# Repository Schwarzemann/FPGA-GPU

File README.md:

# FPGA-GPU
An FPGA GPU designed in KiCAD

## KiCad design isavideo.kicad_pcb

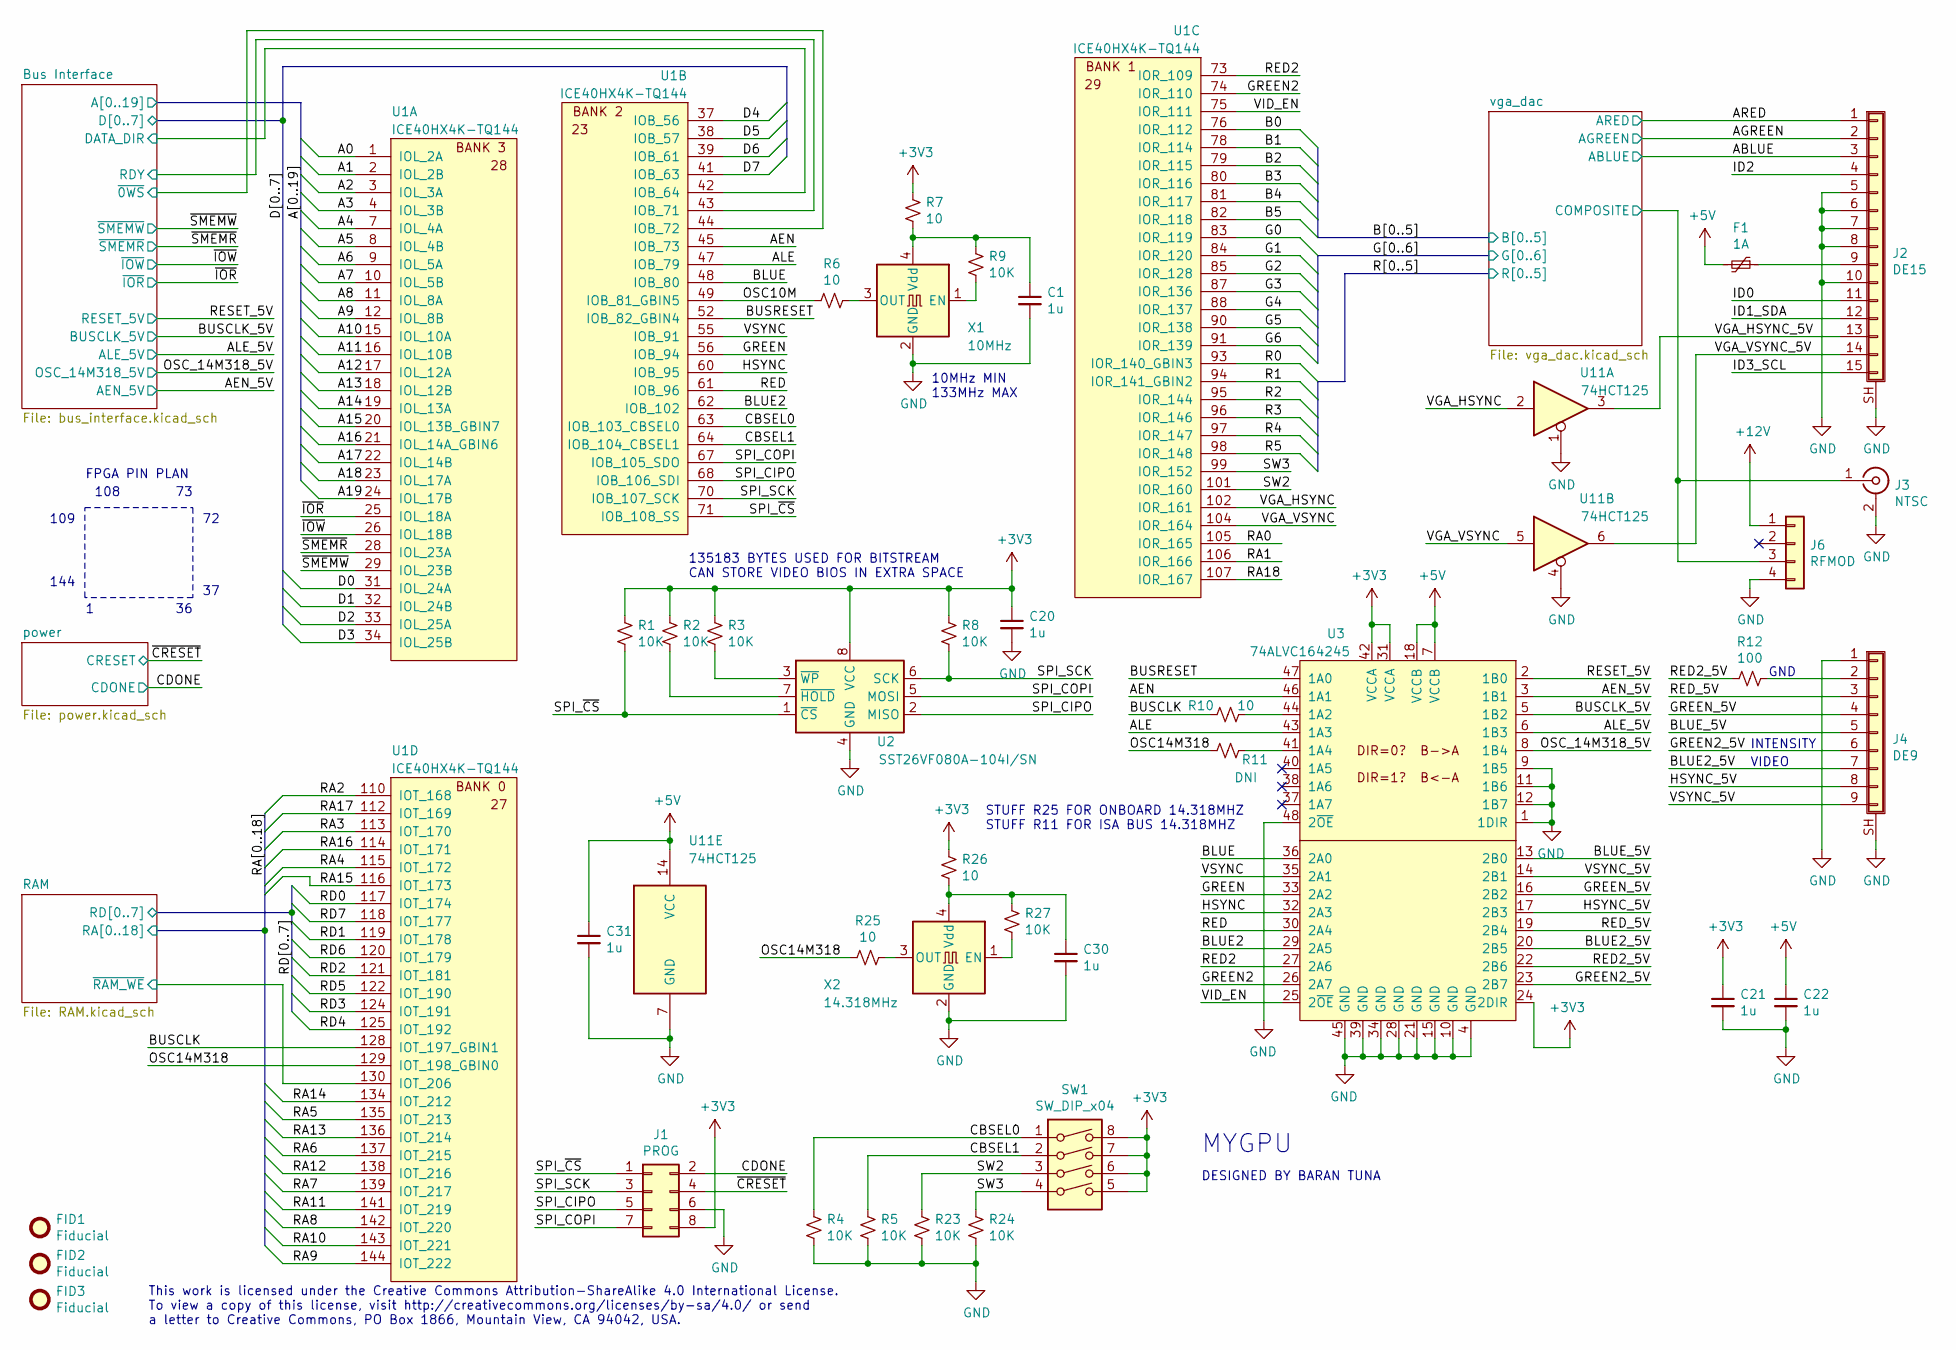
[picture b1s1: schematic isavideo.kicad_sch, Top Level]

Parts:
C1, C20, C21, C22, C30, C31: 1u; CAPC1608X100; Mouser 810-CGA3E1X7R1C105AC
F1: 1A; RESC3216X70; Mouser 530-0ZCJ0050FF2G
FID1, FID2, FID3: Fiducial; Fiducial_1mm_Dia_2mm_Outer
J1: PROG; Pin_Header_Straight_2x04_Pitch2.54mm
J2: DE15; DB15HDFC; Mouser 156-3315-E
J3: NTSC; KOBICONN_161-03X0-E; Mouser 161-0360-E
J4: DE9; DB9FC2; Mouser 152-3409
J6: RFMOD; Pin_Header_Straight_1x04_Pitch2.54mm
R1, R2, R3, R4, R5, R8, R9, R23, R24, R27: 10K; RESC1608X55; Mouser 603-RC0603FR-0710KL
R6, R7, R10, R25, R26: 10; RESC1608X55; Mouser 603-RC0603FR-0710RL
R11: DNI; RESC1608X55; Mouser DNI
R12: 100; RESC1608X55; Mouser 603-RC0603FR-07100RL
SW1: SW_DIP_x04; SW_DIP254P762X635-8; Mouser 706-76PSB04ST
U1: ICE40HX4K-TQ144; TSQFP50P2200X2200X160-144; Mouser 842-ICE40HX4K-TQ144
U2: SST26VF080A-104I/SN; SOP127P620X175-8; Mouser 579-26VF080A-104I/SN
U3: 74ALVC164245; TSSOP50P810X120-48; Mouser 771-74ALVC164245
U11: 74HCT125; TSOP65P640X110-14; Mouser 771-74HCT125PW-T
X1: 10MHz; XTAL320X250X120-4; Mouser 520-ECS-2333-100-BNT
X2: 14.318MHz; XTAL320X250X120-4; Mouser 815-ASE-14.318MLCT

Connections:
+3V3: C20.1, C21.1, J1.8, R1.1, R2.1, R3.1, R7.1, R8.1, R26.1, SW1.5, SW1.6, SW1.7, SW1.8, U2.8 (VCC), U3.24 (2DIR), U3.31 (VCCA), U3.42 (VCCA); also elsewhere on the board
+5V: C22.1, C31.1, F1.2, U3.7 (VCCB), U3.18 (VCCB), U11.14 (VCC); also elsewhere on the board
+12V: J6.1; also elsewhere on the board
/A0: U1.1 (IOL_2A); also elsewhere on the board
/A1: U1.2 (IOL_2B); also elsewhere on the board
/A2: U1.3 (IOL_3A); also elsewhere on the board
/A3: U1.4 (IOL_3B); also elsewhere on the board
/A4: U1.7 (IOL_4A); also elsewhere on the board
/A5: U1.8 (IOL_4B); also elsewhere on the board
/A6: U1.9 (IOL_5A); also elsewhere on the board
/A7: U1.10 (IOL_5B); also elsewhere on the board
/A8: U1.11 (IOL_8A); also elsewhere on the board
/A9: U1.12 (IOL_8B); also elsewhere on the board
/A10: U1.15 (IOL_10A); also elsewhere on the board
/A11: U1.16 (IOL_10B); also elsewhere on the board
/A12: U1.17 (IOL_12A); also elsewhere on the board
/A13: U1.18 (IOL_12B); also elsewhere on the board
/A14: U1.19 (IOL_13A); also elsewhere on the board
/A15: U1.20 (IOL_13B_GBIN7); also elsewhere on the board
/A16: U1.21 (IOL_14A_GBIN6); also elsewhere on the board
/A17: U1.22 (IOL_14B); also elsewhere on the board
/A18: U1.23 (IOL_17A); also elsewhere on the board
/A19: U1.24 (IOL_17B); also elsewhere on the board
/ABLUE: J2.3; also elsewhere on the board
/AEN: U1.45 (IOB_73), U3.46 (1A1)
/AEN_5V: U3.3 (1B1); also elsewhere on the board
/AGREEN: J2.2; also elsewhere on the board
/ALE: U1.47 (IOB_79), U3.43 (1A3)
/ALE_5V: U3.6 (1B3); also elsewhere on the board
/ARED: J2.1; also elsewhere on the board
/B0: U1.76 (IOR_112); also elsewhere on the board
/B1: U1.78 (IOR_114); also elsewhere on the board
/B2: U1.79 (IOR_115); also elsewhere on the board
/B3: U1.80 (IOR_116); also elsewhere on the board
/B4: U1.81 (IOR_117); also elsewhere on the board
/B5: U1.82 (IOR_118); also elsewhere on the board
/BLUE: U1.48 (IOB_80), U3.36 (2A0)
/BLUE2: U1.62 (IOB_102), U3.29 (2A5)
/BLUE2_5V: J4.7, U3.20 (2B5)
/BLUE_5V: J4.5, U3.13 (2B0)
/BUSCLK: R10.2, U1.128 (IOT_197_GBIN1)
/BUSCLK_5V: U3.5 (1B2); also elsewhere on the board
/BUSRESET: U1.52 (IOB_82_GBIN4), U3.47 (1A0)
/Bus Interface/DATA_DIR: U1.42 (IOB_64); also elsewhere on the board
/Bus Interface/RDY: U1.43 (IOB_71); also elsewhere on the board
/Bus Interface/~0WS: U1.44 (IOB_72); also elsewhere on the board
/CBSEL0: R4.1, SW1.1, U1.63 (IOB_103_CBSEL0)
/CBSEL1: R5.1, SW1.2, U1.64 (IOB_104_CBSEL1)
/CDONE: J1.2; also elsewhere on the board
/D0: U1.31 (IOL_24A); also elsewhere on the board
/D1: U1.32 (IOL_24B); also elsewhere on the board
/D2: U1.33 (IOL_25A); also elsewhere on the board
/D3: U1.34 (IOL_25B); also elsewhere on the board
/D4: U1.37 (IOB_56); also elsewhere on the board
/D5: U1.38 (IOB_57); also elsewhere on the board
/D6: U1.39 (IOB_61); also elsewhere on the board
/D7: U1.41 (IOB_63); also elsewhere on the board
/G0: U1.83 (IOR_119); also elsewhere on the board
/G1: U1.84 (IOR_120); also elsewhere on the board
/G2: U1.85 (IOR_128); also elsewhere on the board
/G3: U1.87 (IOR_136); also elsewhere on the board
/G4: U1.88 (IOR_137); also elsewhere on the board
/G5: U1.90 (IOR_138); also elsewhere on the board
/G6: U1.91 (IOR_139); also elsewhere on the board
/GREEN: U1.56 (IOB_94), U3.33 (2A2)
/GREEN2: U1.74 (IOR_110), U3.26 (2A7)
/GREEN2_5V: J4.6, U3.23 (2B7)
/GREEN_5V: J4.4, U3.16 (2B2)
/HSYNC: U1.60 (IOB_95), U3.32 (2A3)
/HSYNC_5V: J4.8, U3.17 (2B3)
/OSC10M: R6.2, U1.49 (IOB_81_GBIN5)
/OSC14M318: R11.2, R25.2, U1.129 (IOT_198_GBIN0)
/OSC_14M318_5V: U3.8 (1B4); also elsewhere on the board
/R0: U1.93 (IOR_140_GBIN3); also elsewhere on the board
/R1: U1.94 (IOR_141_GBIN2); also elsewhere on the board
/R2: U1.95 (IOR_144); also elsewhere on the board
/R3: U1.96 (IOR_146); also elsewhere on the board
/R4: U1.97 (IOR_147); also elsewhere on the board
/R5: U1.98 (IOR_148); also elsewhere on the board
/RA0: U1.105 (IOR_165); also elsewhere on the board
/RA1: U1.106 (IOR_166); also elsewhere on the board
/RA2: U1.110 (IOT_168); also elsewhere on the board
/RA3: U1.113 (IOT_170); also elsewhere on the board
/RA4: U1.115 (IOT_172); also elsewhere on the board
/RA5: U1.135 (IOT_213); also elsewhere on the board
/RA6: U1.137 (IOT_215); also elsewhere on the board
/RA7: U1.139 (IOT_217); also elsewhere on the board
/RA8: U1.142 (IOT_220); also elsewhere on the board
/RA9: U1.144 (IOT_222); also elsewhere on the board
/RA10: U1.143 (IOT_221); also elsewhere on the board
/RA11: U1.141 (IOT_219); also elsewhere on the board
/RA12: U1.138 (IOT_216); also elsewhere on the board
/RA13: U1.136 (IOT_214); also elsewhere on the board
/RA14: U1.134 (IOT_212); also elsewhere on the board
/RA15: U1.116 (IOT_173); also elsewhere on the board
/RA16: U1.114 (IOT_171); also elsewhere on the board
/RA17: U1.112 (IOT_169); also elsewhere on the board
/RA18: U1.107 (IOR_167); also elsewhere on the board
/RAM/~RAM_WE: U1.130 (IOT_206); also elsewhere on the board
/RD0: U1.117 (IOT_174); also elsewhere on the board
/RD1: U1.119 (IOT_178); also elsewhere on the board
/RD2: U1.121 (IOT_181); also elsewhere on the board
/RD3: U1.124 (IOT_191); also elsewhere on the board
/RD4: U1.125 (IOT_192); also elsewhere on the board
/RD5: U1.122 (IOT_190); also elsewhere on the board
/RD6: U1.120 (IOT_179); also elsewhere on the board
/RD7: U1.118 (IOT_177); also elsewhere on the board
/RED: U1.61 (IOB_96), U3.30 (2A4)
/RED2: U1.73 (IOR_109), U3.27 (2A6)
/RED2_5V: R12.2, U3.22 (2B6)
/RED_5V: J4.3, U3.19 (2B4)
/RESET_5V: U3.2 (1B0); also elsewhere on the board
/SPI_CIPO: J1.5, U1.68 (IOB_106_SDI), U2.2 (MISO)
/SPI_COPI: J1.7, U1.67 (IOB_105_SDO), U2.5 (MOSI)
/SPI_SCK: J1.3, R8.2, U1.70 (IOB_107_SCK), U2.6 (SCK)
/SPI_~CS: J1.1, R1.2, U1.71 (IOB_108_SS), U2.1 (~CS)
/SW2: R23.1, SW1.3, U1.101 (IOR_160)
/SW3: R24.1, SW1.4, U1.99 (IOR_152)
/VGA_HSYNC: U1.102 (IOR_161), U11.2
/VGA_HSYNC_5V: J2.13, U11.3
/VGA_VSYNC: U1.104 (IOR_164), U11.5
/VGA_VSYNC_5V: J2.14, U11.6
/VID_EN: U1.75 (IOR_111), U3.25 (2~OE)
/VSYNC: U1.55 (IOB_91), U3.35 (2A1)
/VSYNC_5V: J4.9, U3.14 (2B1)
/vga_dac/COMPOSITE: J3.1 (In), J6.3; also elsewhere on the board
/~CRESET: J1.4; also elsewhere on the board
/~IOR: U1.25 (IOL_18A); also elsewhere on the board
/~IOW: U1.26 (IOL_18B); also elsewhere on the board
/~SMEMR: U1.28 (IOL_23A); also elsewhere on the board
/~SMEMW: U1.29 (IOL_23B); also elsewhere on the board
GND: C1.2, C20.2, C21.2, C22.2, C30.2, C31.2, J1.6, J2.5, J2.6, J2.7, J2.8, J2.10, J2.SH (Shield), J3.2 (Ext), J4.1, J4.SH (Shield), J6.4, R4.2, R5.2, R23.2, R24.2, U2.4 (GND), U3.1 (1DIR), U3.4 (GND), U3.9 (1B5), U3.10 (GND), U3.11 (1B6), U3.12 (1B7), U3.15 (GND), U3.21 (GND), U3.28 (GND), U3.34 (GND), U3.39 (GND), U3.45 (GND), U3.48 (2~OE), U11.1, U11.4, U11.7 (GND), X1.2 (GND), X2.2 (GND); also elsewhere on the board
unnamed: C1.1, R7.2, R9.1, X1.4 (Vdd)
unnamed: C30.1, R26.2, R27.1, X2.4 (Vdd)
unnamed: F1.1, J2.9
unnamed: J4.2, R12.1
unnamed: R2.2, U2.7 (~HOLD)
unnamed: R3.2, U2.3 (~WP)
unnamed: R6.1, X1.3 (OUT)
unnamed: R9.2, X1.1 (EN)
unnamed: R10.1, U3.44 (1A2)
unnamed: R11.1, U3.41 (1A4)
unnamed: R25.1, X2.3 (OUT)
unnamed: R27.2, X2.1 (EN)

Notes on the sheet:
STUFF R25 FOR ONBOARD 14.318MHZ STUFF R11 FOR ISA BUS 14.318MHZ
FPGA PIN PLAN
DESIGNED BY BARAN TUNA
108
VIDEO
GND
144
135183 BYTES USED FOR BITSTREAM CAN STORE VIDEO BIOS IN EXTRA SPACE
109
INTENSITY
MYGPU
This work is licensed under the Creative Commons Attribution-ShareAlike 4.0 International License. To view a copy of this license, visit http://creativecommons.org/licenses/by-sa/4.0/ or send a letter to Creative Commons, PO Box 1866, Mountain View, CA 94042, USA.
10MHz MIN 133MHz MAX

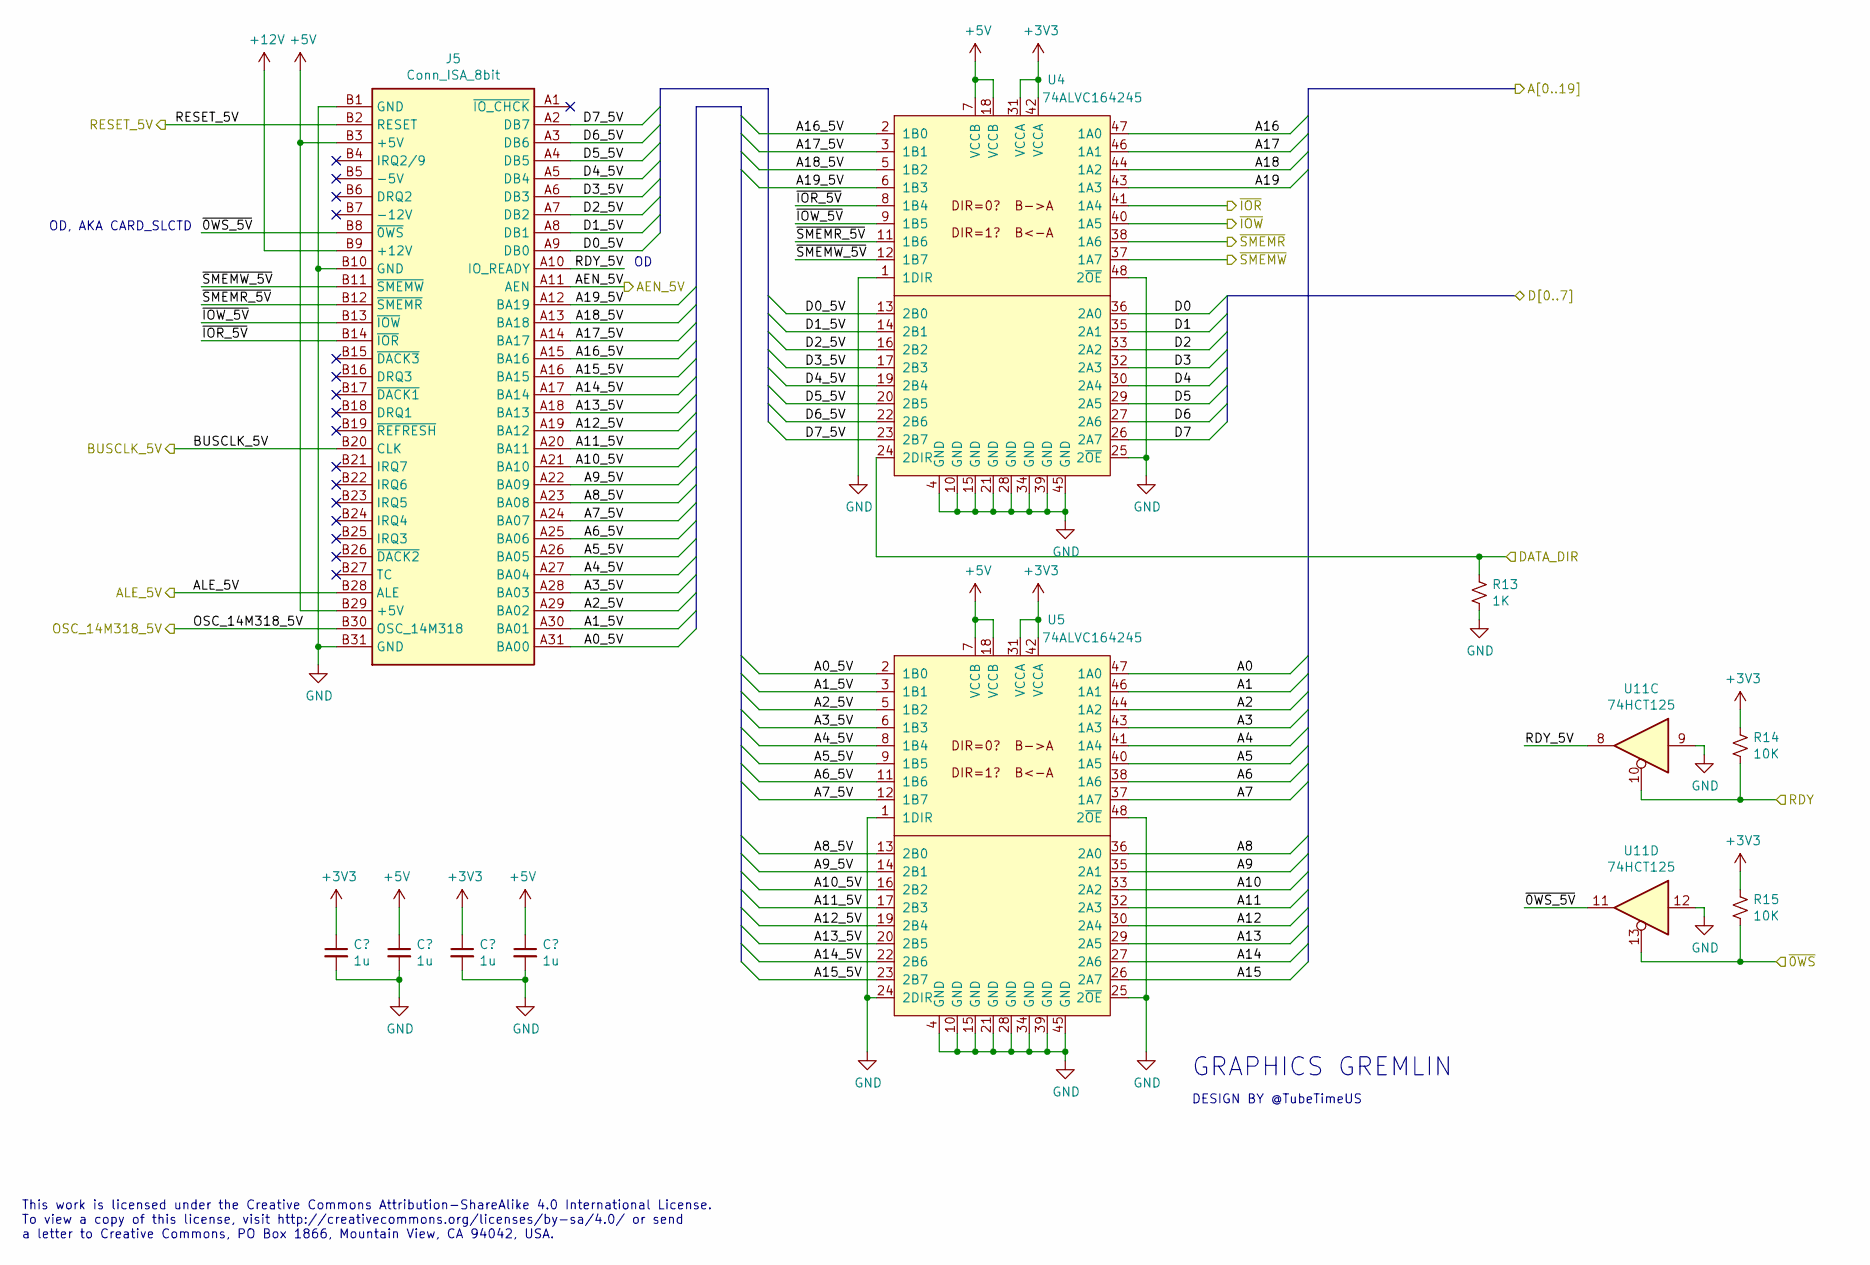
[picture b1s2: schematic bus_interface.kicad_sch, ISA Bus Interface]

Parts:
C23, C24, C25, C26: 1u; CAPC1608X100; Mouser 810-CGA3E1X7R1C105AC
J5: Conn_ISA_8bit; BUS_PC_8BIT
R13: 1K; RESC1608X55; Mouser 603-RC0603FR-071KL
R14, R15: 10K; RESC1608X55; Mouser 603-RC0603FR-0710KL
U4, U5: 74ALVC164245; TSSOP50P810X120-48; Mouser 771-74ALVC164245
U11: 74HCT125; TSOP65P640X110-14; Mouser 771-74HCT125PW-T

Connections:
+3V3: C23.1, C25.1, R14.1, R15.1, U4.31 (VCCA), U4.42 (VCCA), U5.31 (VCCA), U5.42 (VCCA); also elsewhere on the board
+5V: C24.1, C26.1, J5.B3 (+5V), J5.B29 (+5V), U4.7 (VCCB), U4.18 (VCCB), U5.7 (VCCB), U5.18 (VCCB); also elsewhere on the board
+12V: J5.B9 (+12V); also elsewhere on the board
/A0: U5.47 (1A0); also elsewhere on the board
/A1: U5.46 (1A1); also elsewhere on the board
/A2: U5.44 (1A2); also elsewhere on the board
/A3: U5.43 (1A3); also elsewhere on the board
/A4: U5.41 (1A4); also elsewhere on the board
/A5: U5.40 (1A5); also elsewhere on the board
/A6: U5.38 (1A6); also elsewhere on the board
/A7: U5.37 (1A7); also elsewhere on the board
/A8: U5.36 (2A0); also elsewhere on the board
/A9: U5.35 (2A1); also elsewhere on the board
/A10: U5.33 (2A2); also elsewhere on the board
/A11: U5.32 (2A3); also elsewhere on the board
/A12: U5.30 (2A4); also elsewhere on the board
/A13: U5.29 (2A5); also elsewhere on the board
/A14: U5.27 (2A6); also elsewhere on the board
/A15: U5.26 (2A7); also elsewhere on the board
/A16: U4.47 (1A0); also elsewhere on the board
/A17: U4.46 (1A1); also elsewhere on the board
/A18: U4.44 (1A2); also elsewhere on the board
/A19: U4.43 (1A3); also elsewhere on the board
/AEN_5V: J5.A11 (AEN); also elsewhere on the board
/ALE_5V: J5.B28 (ALE); also elsewhere on the board
/BUSCLK_5V: J5.B20 (CLK); also elsewhere on the board
/Bus Interface/A0_5V: J5.A31 (BA00), U5.2 (1B0)
/Bus Interface/A1_5V: J5.A30 (BA01), U5.3 (1B1)
/Bus Interface/A2_5V: J5.A29 (BA02), U5.5 (1B2)
/Bus Interface/A3_5V: J5.A28 (BA03), U5.6 (1B3)
/Bus Interface/A4_5V: J5.A27 (BA04), U5.8 (1B4)
/Bus Interface/A5_5V: J5.A26 (BA05), U5.9 (1B5)
/Bus Interface/A6_5V: J5.A25 (BA06), U5.11 (1B6)
/Bus Interface/A7_5V: J5.A24 (BA07), U5.12 (1B7)
/Bus Interface/A8_5V: J5.A23 (BA08), U5.13 (2B0)
/Bus Interface/A9_5V: J5.A22 (BA09), U5.14 (2B1)
/Bus Interface/A10_5V: J5.A21 (BA10), U5.16 (2B2)
/Bus Interface/A11_5V: J5.A20 (BA11), U5.17 (2B3)
/Bus Interface/A12_5V: J5.A19 (BA12), U5.19 (2B4)
/Bus Interface/A13_5V: J5.A18 (BA13), U5.20 (2B5)
/Bus Interface/A14_5V: J5.A17 (BA14), U5.22 (2B6)
/Bus Interface/A15_5V: J5.A16 (BA15), U5.23 (2B7)
/Bus Interface/A16_5V: J5.A15 (BA16), U4.2 (1B0)
/Bus Interface/A17_5V: J5.A14 (BA17), U4.3 (1B1)
/Bus Interface/A18_5V: J5.A13 (BA18), U4.5 (1B2)
/Bus Interface/A19_5V: J5.A12 (BA19), U4.6 (1B3)
/Bus Interface/D0_5V: J5.A9 (DB0), U4.13 (2B0)
/Bus Interface/D1_5V: J5.A8 (DB1), U4.14 (2B1)
/Bus Interface/D2_5V: J5.A7 (DB2), U4.16 (2B2)
/Bus Interface/D3_5V: J5.A6 (DB3), U4.17 (2B3)
/Bus Interface/D4_5V: J5.A5 (DB4), U4.19 (2B4)
/Bus Interface/D5_5V: J5.A4 (DB5), U4.20 (2B5)
/Bus Interface/D6_5V: J5.A3 (DB6), U4.22 (2B6)
/Bus Interface/D7_5V: J5.A2 (DB7), U4.23 (2B7)
/Bus Interface/DATA_DIR: R13.1, U4.24 (2DIR); also elsewhere on the board
/Bus Interface/RDY: R14.2, U11.10; also elsewhere on the board
/Bus Interface/RDY_5V: J5.A10 (IO_READY), U11.8
/Bus Interface/~0WS_5V: J5.B8 (~0WS), U11.11
/Bus Interface/~0WS: R15.2, U11.13; also elsewhere on the board
/Bus Interface/~IOR_5V: J5.B14 (~IOR), U4.8 (1B4)
/Bus Interface/~IOW_5V: J5.B13 (~IOW), U4.9 (1B5)
/Bus Interface/~SMEMR_5V: J5.B12 (~SMEMR), U4.11 (1B6)
/Bus Interface/~SMEMW_5V: J5.B11 (~SMEMW), U4.12 (1B7)
/D0: U4.36 (2A0); also elsewhere on the board
/D1: U4.35 (2A1); also elsewhere on the board
/D2: U4.33 (2A2); also elsewhere on the board
/D3: U4.32 (2A3); also elsewhere on the board
/D4: U4.30 (2A4); also elsewhere on the board
/D5: U4.29 (2A5); also elsewhere on the board
/D6: U4.27 (2A6); also elsewhere on the board
/D7: U4.26 (2A7); also elsewhere on the board
/OSC_14M318_5V: J5.B30 (OSC_14M318); also elsewhere on the board
/RESET_5V: J5.B2 (RESET); also elsewhere on the board
/~IOR: U4.41 (1A4); also elsewhere on the board
/~IOW: U4.40 (1A5); also elsewhere on the board
/~SMEMR: U4.38 (1A6); also elsewhere on the board
/~SMEMW: U4.37 (1A7); also elsewhere on the board
GND: C23.2, C24.2, C25.2, C26.2, J5.B1 (GND), J5.B10 (GND), J5.B31 (GND), R13.2, U4.1 (1DIR), U4.4 (GND), U4.10 (GND), U4.15 (GND), U4.21 (GND), U4.25 (2~OE), U4.28 (GND), U4.34 (GND), U4.39 (GND), U4.45 (GND), U4.48 (2~OE), U5.1 (1DIR), U5.4 (GND), U5.10 (GND), U5.15 (GND), U5.21 (GND), U5.24 (2DIR), U5.25 (2~OE), U5.28 (GND), U5.34 (GND), U5.39 (GND), U5.45 (GND), U5.48 (2~OE), U11.9, U11.12; also elsewhere on the board

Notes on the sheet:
GRAPHICS GREMLIN
DESIGN BY @TubeTimeUS
OD, AKA CARD_SLCTD
This work is licensed under the Creative Commons Attribution-ShareAlike 4.0 International License. To view a copy of this license, visit http://creativecommons.org/licenses/by-sa/4.0/ or send a letter to Creative Commons, PO Box 1866, Mountain View, CA 94042, USA.

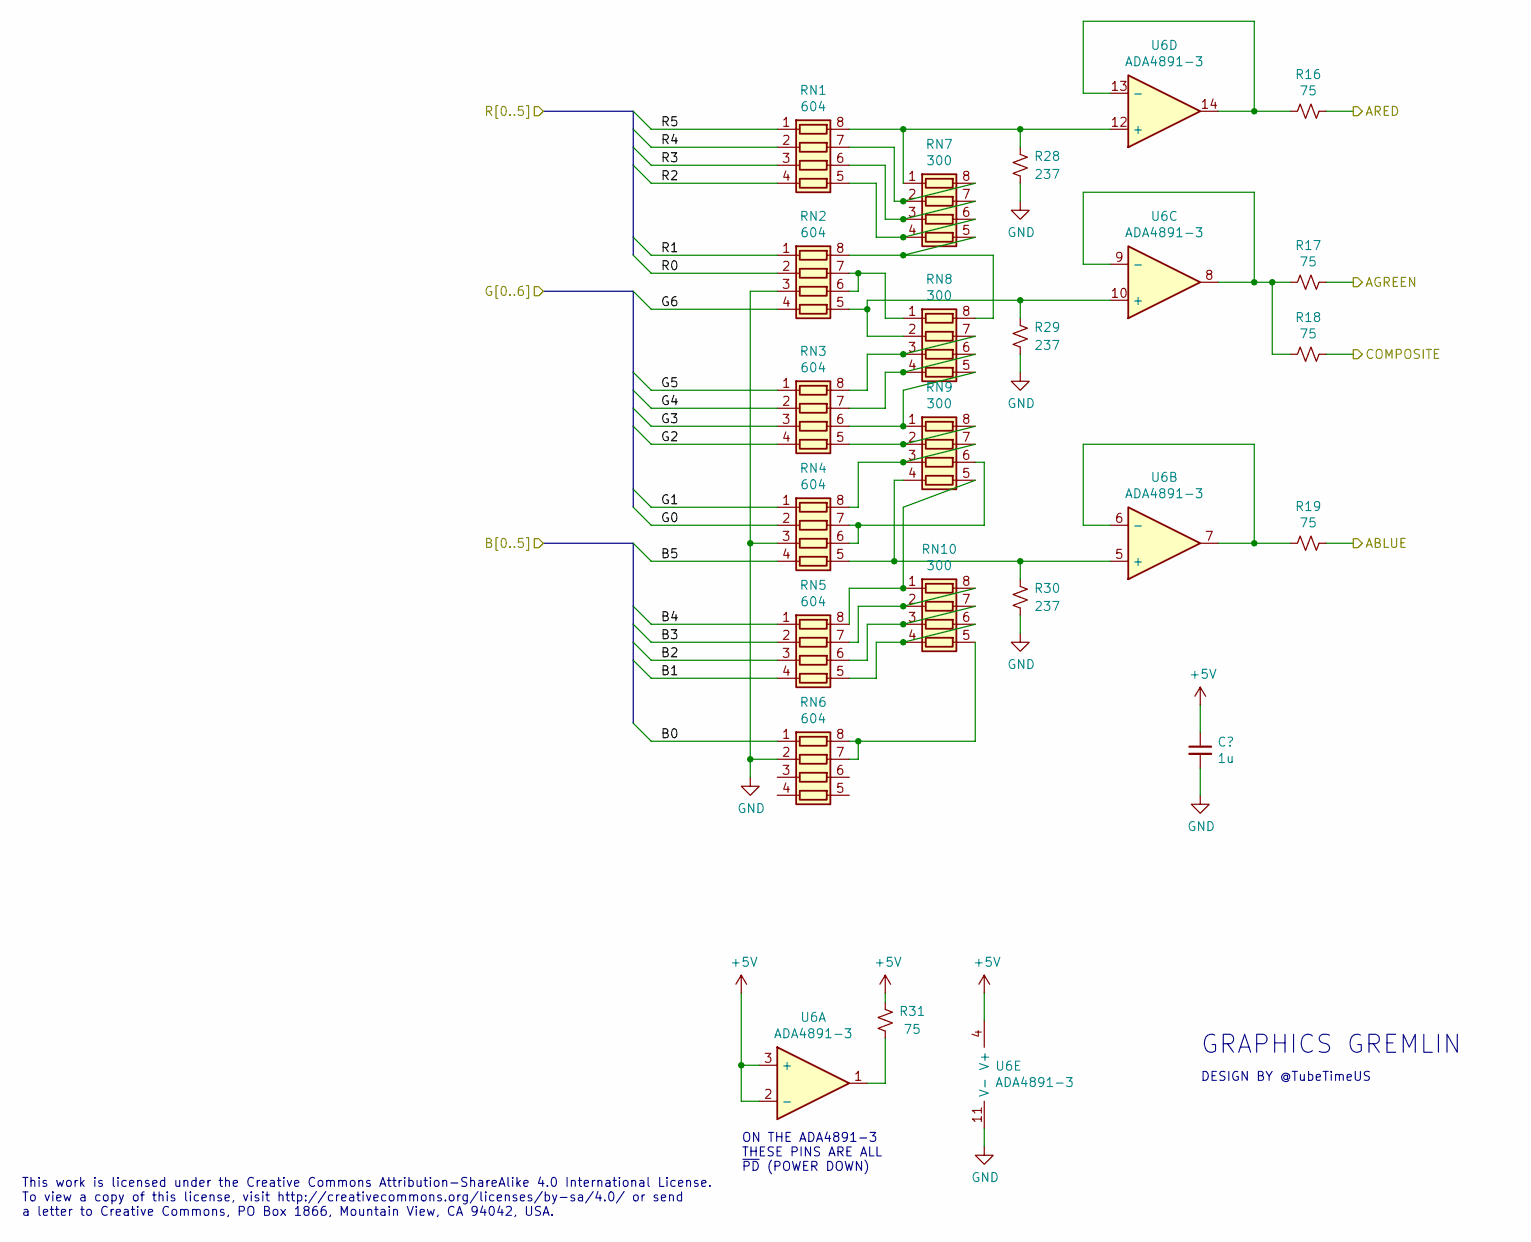
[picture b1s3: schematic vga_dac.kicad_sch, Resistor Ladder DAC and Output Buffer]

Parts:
C27: 1u; CAPC1608X100; Mouser 810-CGA3E1X7R1C105AC
R16, R17, R18, R19, R31: 75; RESC1608X55; Mouser 603-RC0603FR-0775RL
R28, R29, R30: 237; RESC1608X55; Mouser 603-RC0603FR-07237RL
RN1, RN2, RN3, RN4, RN5, RN6: 604; RESCAV80P320X160X70-8; Mouser 652-CAY16-6040F4LF
RN7, RN8, RN9, RN10: 300; RESCAV80P320X160X70-8; Mouser 652-CAY16-3000F4LF
U6: ADA4891-3; SOP127P620X175-14; Mouser 584-ADA4891-3ARZ

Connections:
+5V: C27.1, R31.2, U6.2 (-), U6.3 (+), U6.4 (V+); also elsewhere on the board
/ABLUE: R19.1; also elsewhere on the board
/AGREEN: R17.1; also elsewhere on the board
/ARED: R16.1; also elsewhere on the board
/B0: RN6.1 (R1.1); also elsewhere on the board
/B1: RN5.4 (R4.1); also elsewhere on the board
/B2: RN5.3 (R3.1); also elsewhere on the board
/B3: RN5.2 (R2.1); also elsewhere on the board
/B4: RN5.1 (R1.1); also elsewhere on the board
/B5: RN4.4 (R4.1); also elsewhere on the board
/G0: RN4.2 (R2.1); also elsewhere on the board
/G1: RN4.1 (R1.1); also elsewhere on the board
/G2: RN3.4 (R4.1); also elsewhere on the board
/G3: RN3.3 (R3.1); also elsewhere on the board
/G4: RN3.2 (R2.1); also elsewhere on the board
/G5: RN3.1 (R1.1); also elsewhere on the board
/G6: RN2.4 (R4.1); also elsewhere on the board
/R0: RN2.2 (R2.1); also elsewhere on the board
/R1: RN2.1 (R1.1); also elsewhere on the board
/R2: RN1.4 (R4.1); also elsewhere on the board
/R3: RN1.3 (R3.1); also elsewhere on the board
/R4: RN1.2 (R2.1); also elsewhere on the board
/R5: RN1.1 (R1.1); also elsewhere on the board
/vga_dac/COMPOSITE: R18.1; also elsewhere on the board
GND: C27.2, R28.1, R29.1, R30.1, RN2.3 (R3.1), RN4.3 (R3.1), RN6.2 (R2.1), U6.11 (V-); also elsewhere on the board
unnamed: R16.2, U6.13 (-), U6.14
unnamed: R17.2, R18.2, U6.8, U6.9 (-)
unnamed: R19.2, U6.6 (-), U6.7
unnamed: R28.2, RN1.8 (R1.2), RN7.1 (R1.1), U6.12 (+)
unnamed: R29.2, RN2.5 (R4.2), RN8.2 (R2.1), U6.10 (+)
unnamed: R30.2, RN4.5 (R4.2), RN9.4 (R4.1), U6.5 (+)
unnamed: R31.1, U6.1
unnamed: RN1.5 (R4.2), RN7.4 (R4.1), RN7.6 (R3.2)
unnamed: RN1.6 (R3.2), RN7.3 (R3.1), RN7.7 (R2.2)
unnamed: RN1.7 (R2.2), RN7.2 (R2.1), RN7.8 (R1.2)
unnamed: RN2.6 (R3.2), RN2.7 (R2.2), RN8.1 (R1.1)
unnamed: RN2.8 (R1.2), RN7.5 (R4.2), RN8.8 (R1.2)
unnamed: RN3.5 (R4.2), RN9.2 (R2.1), RN9.8 (R1.2)
unnamed: RN3.6 (R3.2), RN8.5 (R4.2), RN9.1 (R1.1)
unnamed: RN3.7 (R2.2), RN8.4 (R4.1), RN8.6 (R3.2)
unnamed: RN3.8 (R1.2), RN8.3 (R3.1), RN8.7 (R2.2)
unnamed: RN4.6 (R3.2), RN4.7 (R2.2), RN9.6 (R3.2)
unnamed: RN4.8 (R1.2), RN9.3 (R3.1), RN9.7 (R2.2)
unnamed: RN5.8 (R1.2), RN9.5 (R4.2), RN10.1 (R1.1)
unnamed: RN5.7 (R2.2), RN10.2 (R2.1), RN10.8 (R1.2)
unnamed: RN5.6 (R3.2), RN10.3 (R3.1), RN10.7 (R2.2)
unnamed: RN5.5 (R4.2), RN10.4 (R4.1), RN10.6 (R3.2)
unnamed: RN6.7 (R2.2), RN6.8 (R1.2), RN10.5 (R4.2)

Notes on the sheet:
ON THE ADA4891-3 THESE PINS ARE ALL ~{PD} (POWER DOWN)
This work is licensed under the Creative Commons Attribution-ShareAlike 4.0 International License. To view a copy of this license, visit http://creativecommons.org/licenses/by-sa/4.0/ or send a letter to Creative Commons, PO Box 1866, Mountain View, CA 94042, USA.
DESIGN BY @TubeTimeUS
GRAPHICS GREMLIN

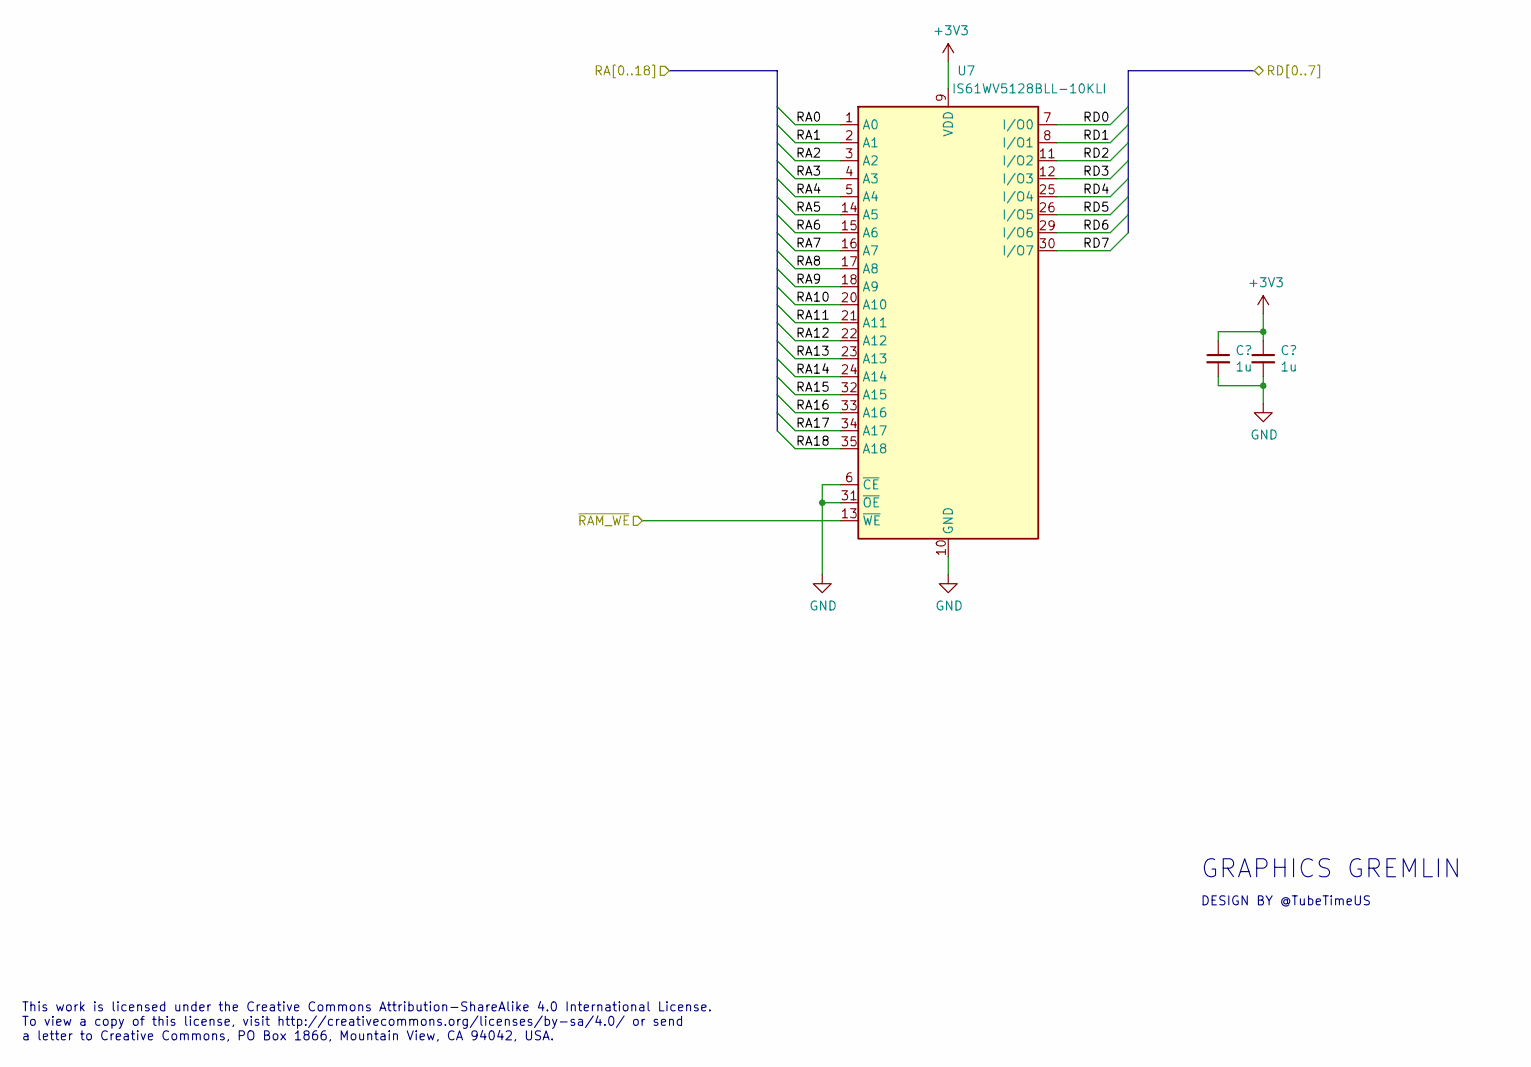
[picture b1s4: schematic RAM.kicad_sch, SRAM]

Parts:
C28, C29: 1u; CAPC1608X100; Mouser 810-CGA3E1X7R1C105AC
U7: IS61WV5128BLL-10KLI; SOJ127P1118X376-36; Mouser 870-61WV5128B10KLI

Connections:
+3V3: C28.1, C29.1, U7.9 (VDD), U7.27 (VDD); also elsewhere on the board
/RA0: U7.1 (A0); also elsewhere on the board
/RA1: U7.2 (A1); also elsewhere on the board
/RA2: U7.3 (A2); also elsewhere on the board
/RA3: U7.4 (A3); also elsewhere on the board
/RA4: U7.5 (A4); also elsewhere on the board
/RA5: U7.14 (A5); also elsewhere on the board
/RA6: U7.15 (A6); also elsewhere on the board
/RA7: U7.16 (A7); also elsewhere on the board
/RA8: U7.17 (A8); also elsewhere on the board
/RA9: U7.18 (A9); also elsewhere on the board
/RA10: U7.20 (A10); also elsewhere on the board
/RA11: U7.21 (A11); also elsewhere on the board
/RA12: U7.22 (A12); also elsewhere on the board
/RA13: U7.23 (A13); also elsewhere on the board
/RA14: U7.24 (A14); also elsewhere on the board
/RA15: U7.32 (A15); also elsewhere on the board
/RA16: U7.33 (A16); also elsewhere on the board
/RA17: U7.34 (A17); also elsewhere on the board
/RA18: U7.35 (A18); also elsewhere on the board
/RAM/~RAM_WE: U7.13 (~WE); also elsewhere on the board
/RD0: U7.7 (I/O0); also elsewhere on the board
/RD1: U7.8 (I/O1); also elsewhere on the board
/RD2: U7.11 (I/O2); also elsewhere on the board
/RD3: U7.12 (I/O3); also elsewhere on the board
/RD4: U7.25 (I/O4); also elsewhere on the board
/RD5: U7.26 (I/O5); also elsewhere on the board
/RD6: U7.29 (I/O6); also elsewhere on the board
/RD7: U7.30 (I/O7); also elsewhere on the board
GND: C28.2, C29.2, U7.6 (~CE), U7.10 (GND), U7.28 (GND), U7.31 (~OE); also elsewhere on the board

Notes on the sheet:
This work is licensed under the Creative Commons Attribution-ShareAlike 4.0 International License. To view a copy of this license, visit http://creativecommons.org/licenses/by-sa/4.0/ or send a letter to Creative Commons, PO Box 1866, Mountain View, CA 94042, USA.
GRAPHICS GREMLIN
DESIGN BY @TubeTimeUS

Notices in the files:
isavideo.kicad_pcb:
Copyright (C) 2021 Tube Time
License. See https://creativecommons.org/licenses/by-sa/4.0
This work is licensed under a Creative Commons Attribution-ShareAlike 4.0 International
